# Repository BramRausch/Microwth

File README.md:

# Microwth
The Microwth is a soilless indoor microgreen farm with build-in lighting and watering pump, the user interface provides an easy way to customize growing conditions to your liking.

The goal of this project is to create an open source platform to easily grow microgreens with a continuous harvesting cycle without too much intervention. To reach this goal I will test different lighting solutions, create multiple designs with different materials and optimize the growing cycle.

This repository hosts all hardware and software files of the platform, the current plastform runs standalone. In the future we would also like to connect the Microwth to the internet and develop a web application to manage the farms to notify the user about the grow conditions or tasks that are required.

Check out the [Hackaday.io](https://hackaday.io/project/168342-microwth-automated-microgreen-farm) page for more information and images of the build process.

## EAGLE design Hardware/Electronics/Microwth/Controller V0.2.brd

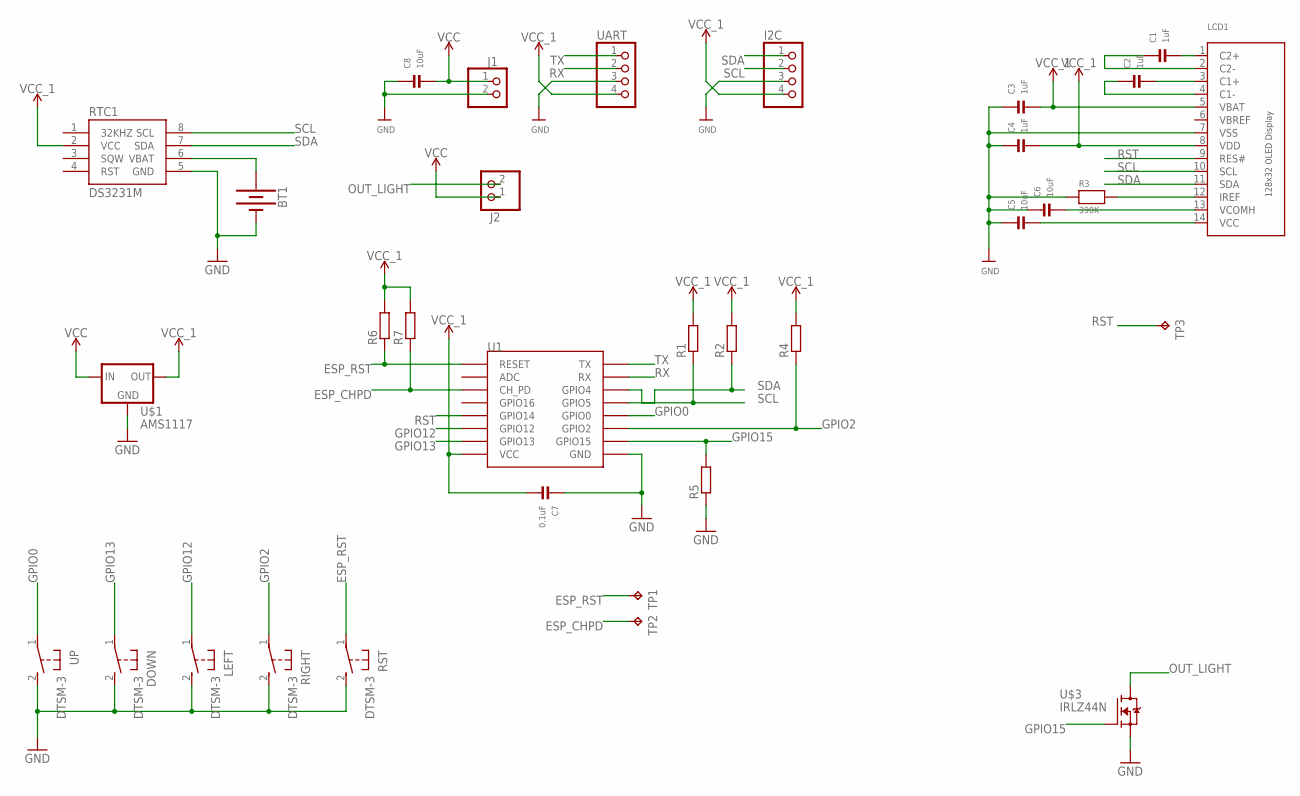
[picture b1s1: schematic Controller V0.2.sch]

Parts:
BT1: BATTERY-20MM_PTH; BATTCOM_20MM_PTH
C1, C2, C3, C4: 1uF; 0805
C5, C6, C8: 10uF; 0805
C7: 0.1uF; 0805
DOWN: DTSM-3
I2C: PINHD-1X4; 1X04
J1, J2: PINHD-1X2; 1X02
LCD1: DISP_OLED_UG-2832HSWEG02; UG-2832HSWEG02_WRAPUNDER
LEFT: DTSM-3
R1, R2, R4, R5, R6, R7: R-EU_R0805; R0805
R3: 390K; 0805
RIGHT: DTSM-3
RST: DTSM-3
RTC1: DS3231M; SO08
TP1, TP2, TP3: TPB1,27; B1,27
U1: ESP12SMD; ESP12-SMD
U$1: AMS1117; SOT223
U$3: IRLZ44N; TO220
UART: PINHD-1X4; 1X04
UP: DTSM-3

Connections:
ESP_CHPD: R7.1, TP2.TP, U1.CH_PD
ESP_RST: R6.1, RST.1, TP1.TP, U1.RESET
GND: BT1.2 (-), C3.1, C4.1, C5.1, C6.1, C7.1, C8.1, DOWN.2, I2C.3, J1.2, LCD1.7 (VSS), LEFT.2, R3.1, R5.1, RIGHT.2, RST.2, RTC1.5 (GND), U1.GND, U$1.1 (GND), U$3.3 (S), UART.3, UP.2
GPIO0: U1.GPIO0, UP.1
GPIO2: R4.1, RIGHT.1, U1.GPIO2
GPIO12: LEFT.1, U1.GPIO12
GPIO13: DOWN.1, U1.GPIO13
GPIO15: R5.2, U1.GPIO15, U$3.1 (G)
unnamed: C1.2, LCD1.1 (C2+)
unnamed: C1.1, LCD1.2 (C2-)
unnamed: C2.2, LCD1.3 (C1+)
unnamed: C2.1, LCD1.4 (C1-)
unnamed: C6.2, LCD1.13 (VCOMH)
unnamed: C5.2, LCD1.14 (VCC)
unnamed: LCD1.12 (IREF), R3.2
unnamed: BT1.1 (+), RTC1.6 (VBAT)
OUT_LIGHT: J2.2, U$3.2 (D)
RST: LCD1.9 (RES#), TP3.TP, U1.GPIO14
RX: U1.RXD0 (RX), UART.2
SCL: I2C.2, LCD1.10 (SCL), R1.1, RTC1.8 (SCL), U1.GPIO4
SDA: I2C.1, LCD1.11 (SDA), R2.1, RTC1.7 (SDA), U1.GPIO5
TX: U1.TXD0 (TX), UART.1
VBREF: LCD1.6 (VBREF)
VCC: C8.2, J1.1, J2.1, U$1.3 (IN)
VCC_1: C3.2, C4.2, C7.2, I2C.4, LCD1.5 (VBAT), LCD1.8 (VDD), R1.2, R2.2, R4.2, R6.2, R7.2, RTC1.2 (VCC), U1.VCC, U$1.2 (OUT), UART.4

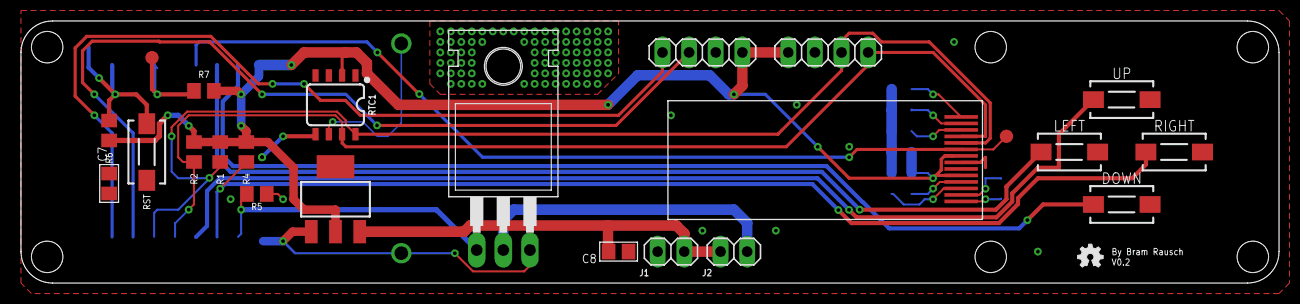
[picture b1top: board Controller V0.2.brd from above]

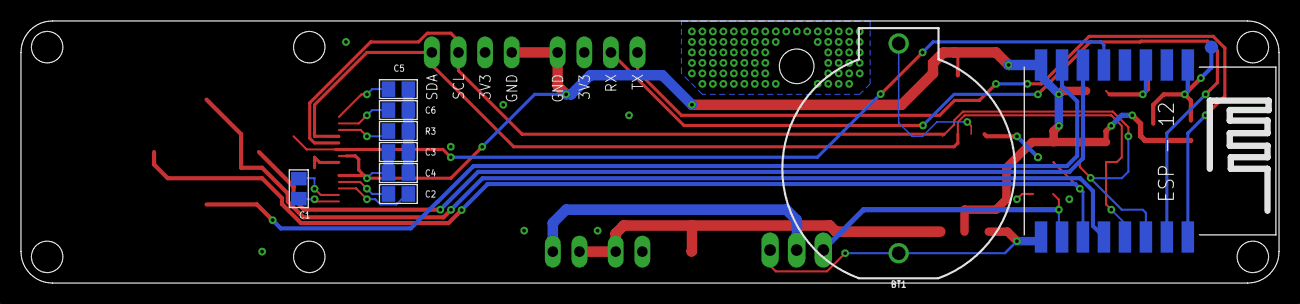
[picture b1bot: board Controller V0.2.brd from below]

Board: 2 copper layers, 120.0 x 25.0 mm, 34 parts (10 on the bottom side), 24 nets.

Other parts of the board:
U$4: OSHW-LOGO-MINI

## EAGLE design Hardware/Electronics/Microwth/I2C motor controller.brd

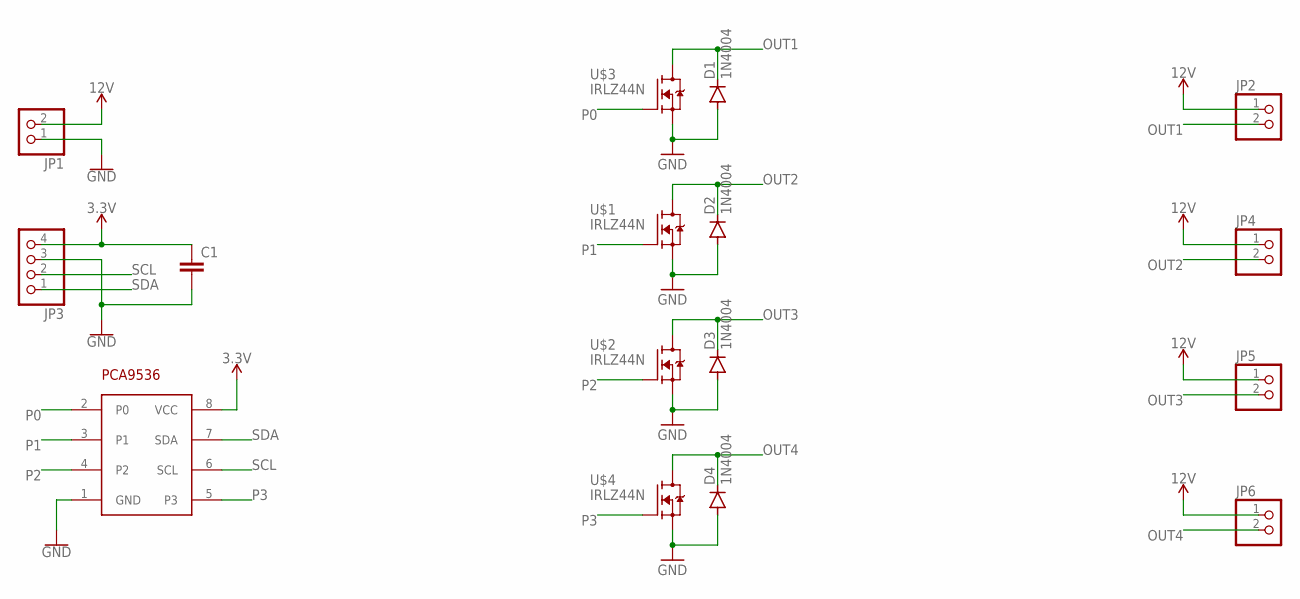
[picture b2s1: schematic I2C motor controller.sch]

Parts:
C1: C-EUC0805; C0805
D1, D2, D3, D4: 1N4004; DO41-10
JP1, JP2, JP4, JP5, JP6: PINHD-1X2; 1X02
JP3: PINHD-1X4; 1X04
PCA9536: PCA9536DGK; SOP65P490X110-8N
U$1, U$2, U$3, U$4: IRLZ44N; TO220

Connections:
3.3V: C1.1, JP3.4, PCA9536.8 (VCC)
12V: JP1.2, JP2.1, JP4.1, JP5.1, JP6.1
GND: C1.2, D1.A, D2.A, D3.A, D4.A, JP1.1, JP3.3, PCA9536.1 (GND), U$1.3 (S), U$2.3 (S), U$3.3 (S), U$4.3 (S)
OUT1: D1.C, JP2.2, U$3.2 (D)
OUT2: D2.C, JP4.2, U$1.2 (D)
OUT3: D3.C, JP5.2, U$2.2 (D)
OUT4: D4.C, JP6.2, U$4.2 (D)
P0: PCA9536.2 (P0), U$3.1 (G)
P1: PCA9536.3 (P1), U$1.1 (G)
P2: PCA9536.4 (P2), U$2.1 (G)
P3: PCA9536.5 (P3), U$4.1 (G)
SCL: JP3.2, PCA9536.6 (SCL)
SDA: JP3.1, PCA9536.7 (SDA)

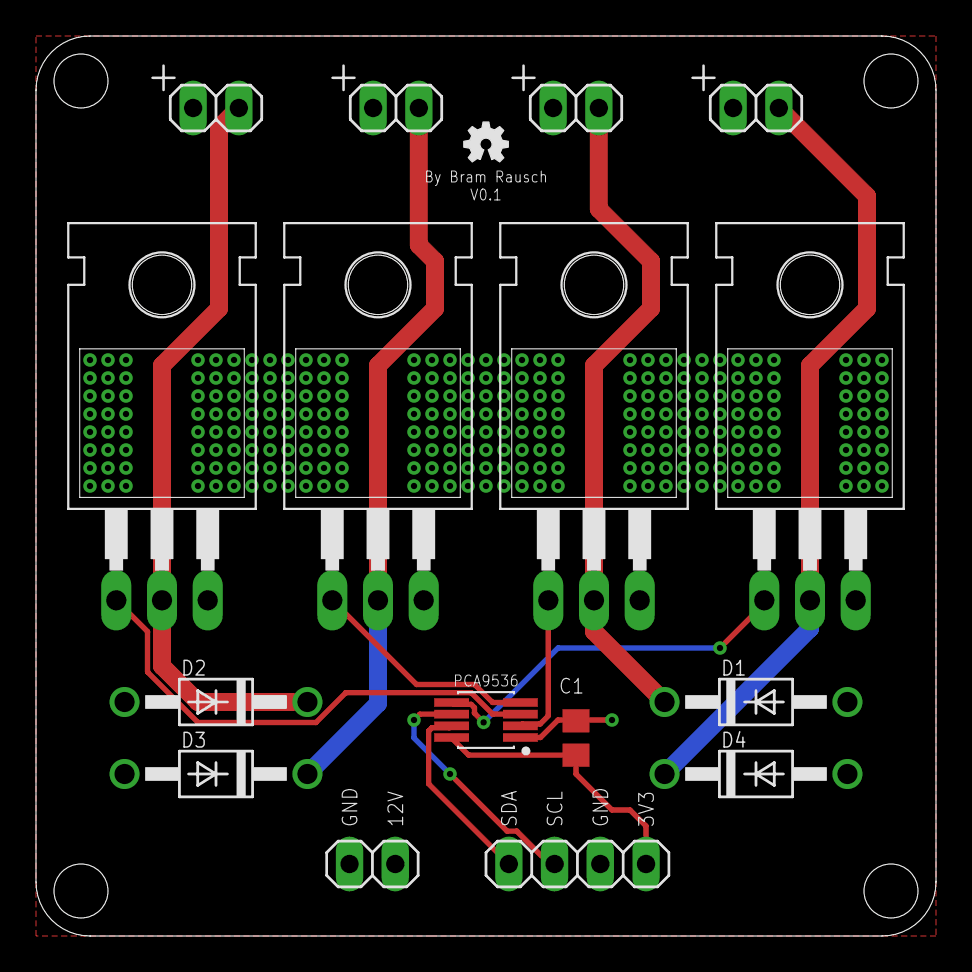
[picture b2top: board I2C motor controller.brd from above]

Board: 2 copper layers, 50.0 x 50.0 mm, 17 parts (0 on the bottom side), 13 nets.

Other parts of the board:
U$5: OSHW-LOGO-MINI

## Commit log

2019-11-12 Microwth standalone software
    initial commit
2019-11-16 V0.2
    * changed menu structure
    * added grow mode (set pump interval, pump duration, light on time and light off time)
    * improved comments
    * centered text
2019-12-06 new file: Microwth/DS3231.ino new file: Microwth/Display.ino modified: Microwth/Microwth.ino new file: Microwth/MotorController.ino V0.3 Setting up proper version control
2019-12-06 Added hardware and imagary
2019-12-06 Added eagle files
2019-12-08 created dev branch
2019-12-08 bug fix unable to set motor interval

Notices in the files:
parts and their libraries:
SparkFun-Batteries: Licensing: Creative Commons ShareAlike 4.0 International - https://creativecommons.org/licenses/by-sa/4.0
